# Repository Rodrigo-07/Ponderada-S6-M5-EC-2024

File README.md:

# Ponderada-S6-M5-EC-2024

Nome: Rodrigo Sales Freire dos Santos

Repositorio para a entrega da atividade de Ponderada-S6-M5-EC-2024. Para concluir a atividade desenvolvi uma placa PCI que contem um Raspberry Pico que a partir da leitura da luminosidade do ambiente, aciona algun dispositivo de saida atraves de um rele e um transistor. O projeto foi desenvolvido no software KiCad.

# Imagens do Projeto

## Desenho Esquematico

## Placa PCI

# Imagem 3D

# Lista de Materiais

| Reference      | Value         | Datasheet                                                    | Footprint                                                      | Qty | DNP |
|----------------|---------------|--------------------------------------------------------------|----------------------------------------------------------------|-----|-----|
| `Led Vermelha`           | LED           | ~                                                            | LED_THT:LED_D3.0mm                                             | 1   |     |
| `Diodo`           | D             | ~                                                            | Diode_SMD:D_MiniMELF                                          | 1   |     |
| `Pin out`           | Pin Out       | ~                                                            | Connector_PinHeader_1.00mm:PinHeader_1x01_P1.00mm_Vertical    | 1   |     |
| `Relay`           | Relay_SPST-NO | ~                                                            | Relay_THT:Relay_SPST_Schrack-RT1-FormA_RM5mm                  | 1   |     |
| `Photo Resistor` | A1050       | [Datasheet](http://cdn-reichelt.de/documents/datenblatt/A500/A106012.pdf) | OptoDevice:R_LDR_D6.4mm_P3.4mm_Vertical                       | 1   |     |
| `Transistor BC548`           | BC548         | [Datasheet](https://www.onsemi.com/pub/Collateral/BC550-D.pdf) | Package_TO_SOT_THT:TO-92_Inline                               | 1   |     |
| `Resistor 240Ω`           | 240Ω          | ~                                                            | Resistor_THT:R_Axial_DIN0204_L3.6mm_D1.6mm_P7.62mm_Horizontal | 1   |     |
| `Resistor 10kΩ`           | 10kΩ          | ~                                                            | Resistor_THT:R_Axial_DIN0204_L3.6mm_D1.6mm_P7.62mm_Horizontal | 1   |     |
| `Raspberry Pico`           | Pico          |                                                              | MCU_RaspberryPi_and_Boards:RPi_Pico_SMD_TH                    | 1   |     |

# Arquivos

Todos os arquivos de execução do projeto no Kicad estão disponiveis na pasta "Arquivos" deste repositorio.

- Arquivo do Kicad: Ponderada Semana 6.kicad_pro
- Desenho Esquematico: Ponderada Semana 6.kicad_sch
- PCB: Ponderada Semana 6.kicad_pcb

Os arquvis gerados para a fabricação da placa PCI estão disponiveis na pasta "Gerbers" deste repositorio.

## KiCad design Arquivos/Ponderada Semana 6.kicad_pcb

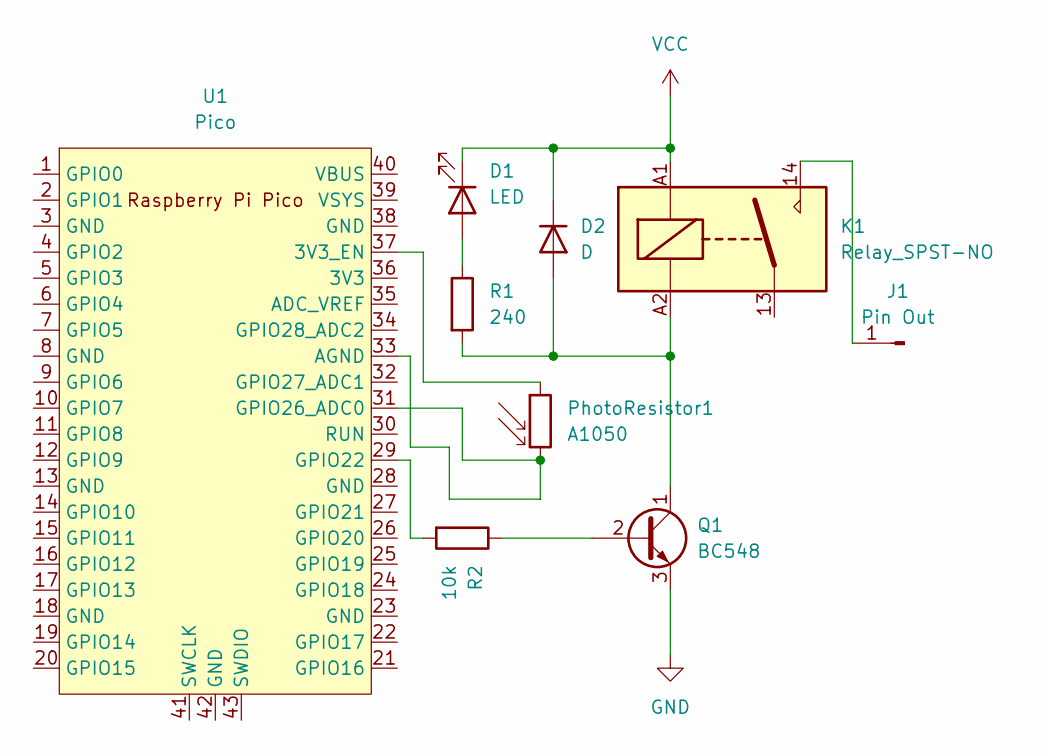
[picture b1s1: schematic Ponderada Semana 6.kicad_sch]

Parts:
D1: LED; LED_D3.0mm
D2: D; D_MiniMELF
J1: Pin Out; PinHeader_1x01_P1.00mm_Vertical
K1: Relay_SPST-NO; Relay_SPST_Schrack-RT1-FormA_RM5mm
PhotoResistor1: A1050; R_LDR_D6.4mm_P3.4mm_Vertical
Q1: BC548; TO-92_Inline
R1: 240; R_Axial_DIN0204_L3.6mm_D1.6mm_P7.62mm_Horizontal
R2: 10k; R_Axial_DIN0204_L3.6mm_D1.6mm_P7.62mm_Horizontal
U1: Pico; RPi_Pico_SMD_TH

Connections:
GND: Q1.3 (E)
unnamed: D1.2 (A), R1.1
unnamed: D2.2 (A), K1.A2, Q1.1 (C), R1.2
unnamed: J1.1, K1.14
unnamed: Q1.2 (B), R2.1
unnamed: PhotoResistor1.1, U1.37 (3V3_EN)
unnamed: PhotoResistor1.2, U1.31 (GPIO26_ADC0), U1.33 (AGND)
unnamed: R2.2, U1.29 (GPIO22)
VCC: D1.1 (K), D2.1 (K), K1.A1

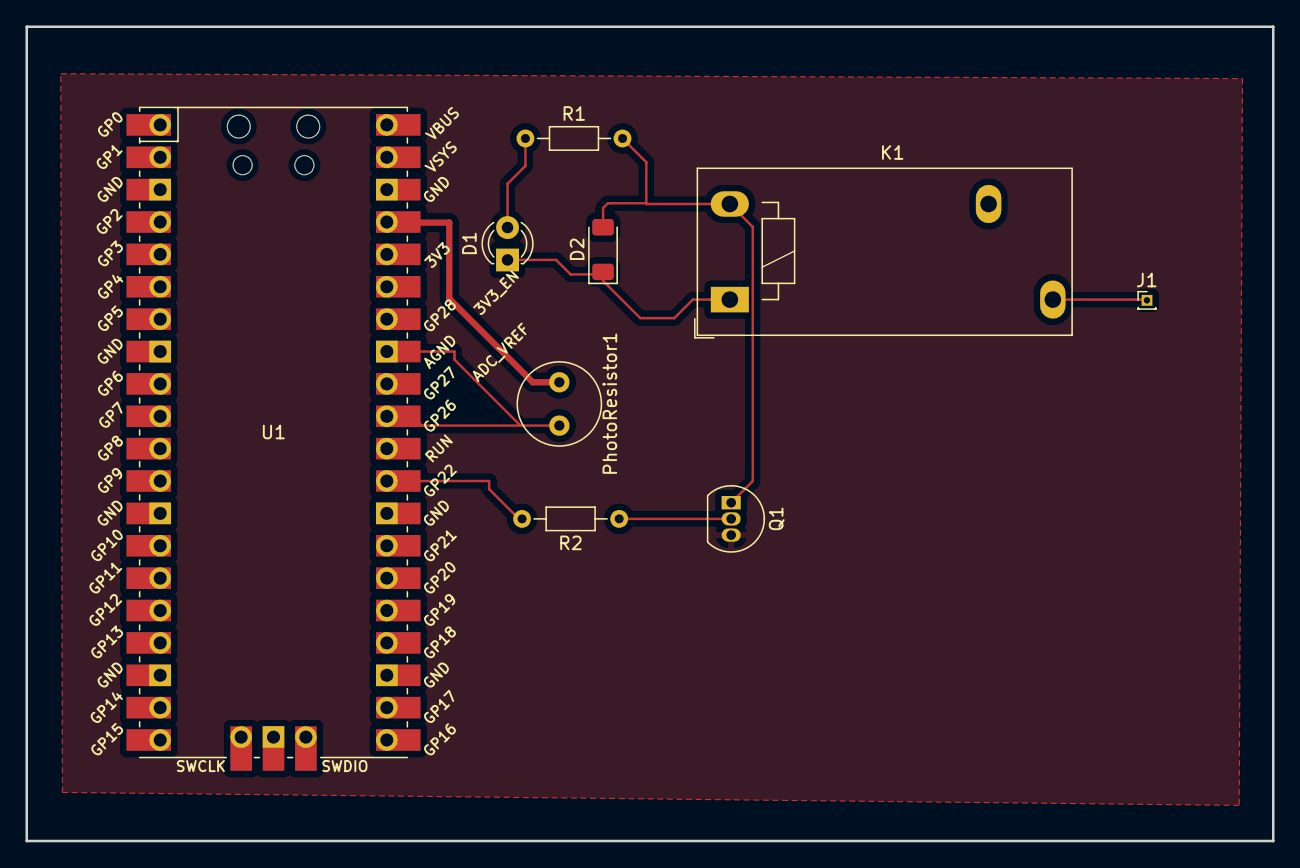
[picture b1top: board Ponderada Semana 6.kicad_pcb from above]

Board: 2 copper layers, 97.8 x 63.9 mm, 9 parts (0 on the bottom side), 8 nets.

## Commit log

2024-04-01 Arquivos
2024-04-01 Alteração caminho das pascas
